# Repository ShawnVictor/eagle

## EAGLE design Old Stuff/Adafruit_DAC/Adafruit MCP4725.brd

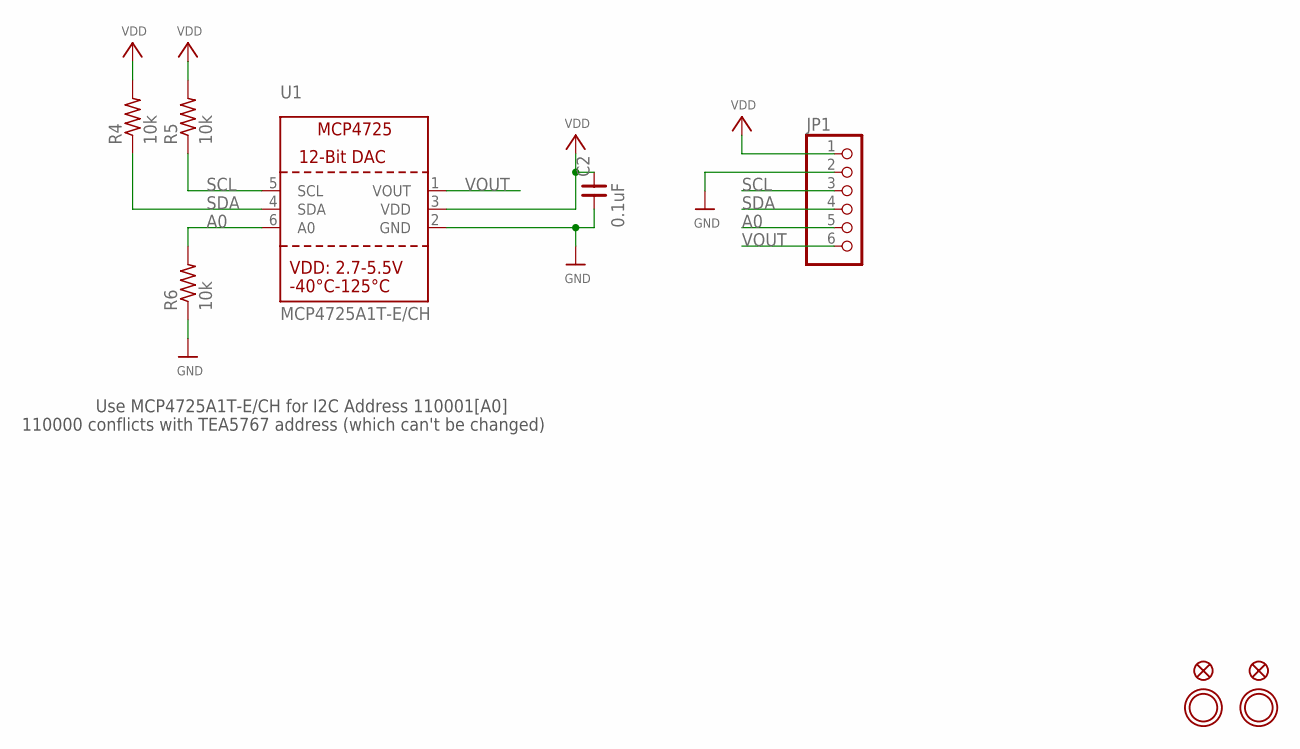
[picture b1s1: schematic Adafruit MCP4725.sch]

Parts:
C2: 0.1uF; 0805
FID1, FID2: FIDUCIAL""; FIDUCIAL_1MM
JP1: HEADER-1X670MIL; 1X06_ROUND_70
R4, R5, R6: 10k; R0805
U1: MCP4725A1T-E/CH; SOT23-6
U$7, U$8: MOUNTINGHOLE2.5; MOUNTINGHOLE_2.5_PLATED

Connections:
A0: JP1.5, R6.2, U1.6 (A0)
GND: C2.1, JP1.2, R6.1, U1.2 (GND)
SCL: JP1.3, R5.1, U1.5 (SCL)
SDA: JP1.4, R4.1, U1.4 (SDA)
VDD: C2.2, JP1.1, R4.2, R5.2, U1.3 (VDD)
VOUT: JP1.6, U1.1 (VOUT)

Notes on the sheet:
Use MCP4725A1T-E/CH for I2C Address 110001[A0]
110000 conflicts with TEA5767 address (which can't be changed)

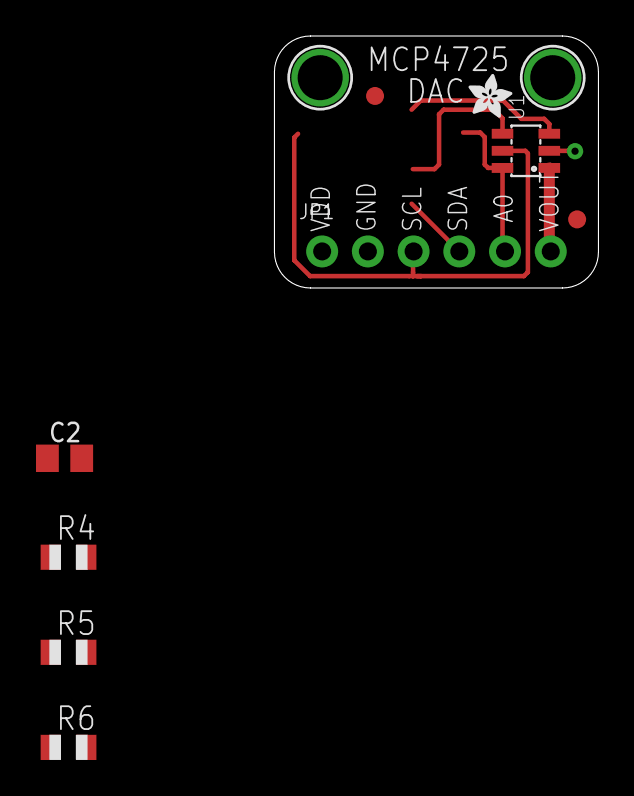
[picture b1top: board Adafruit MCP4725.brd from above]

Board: 2 copper layers, 18.0 x 14.0 mm, 11 parts (0 on the bottom side), 6 nets.

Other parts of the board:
U$11: ADAFRUIT_2.5MM

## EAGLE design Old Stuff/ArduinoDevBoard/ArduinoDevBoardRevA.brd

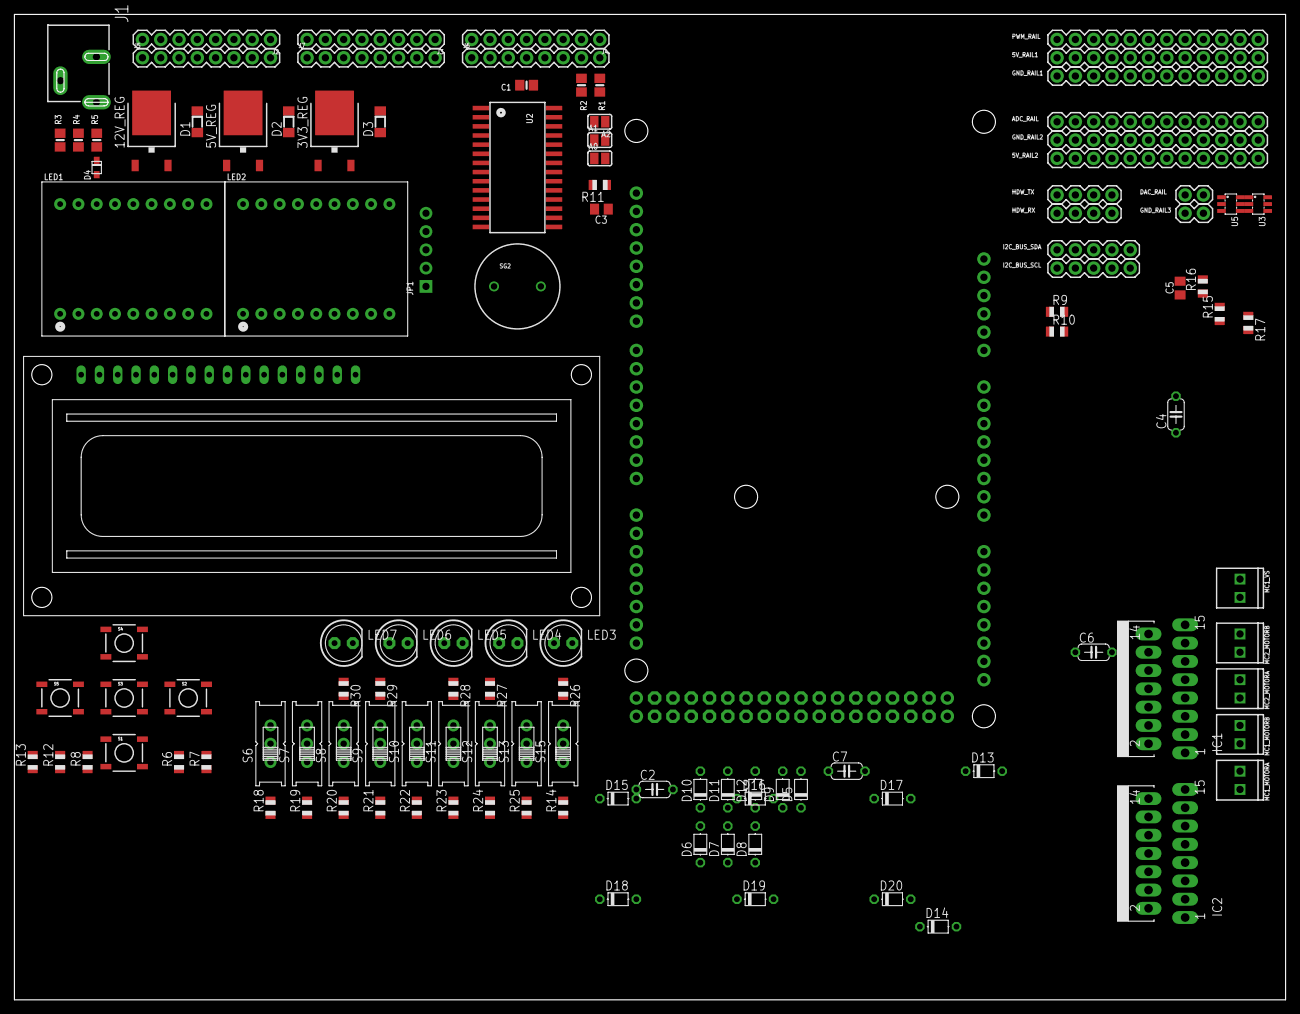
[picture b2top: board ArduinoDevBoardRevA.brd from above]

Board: 2 copper layers, 176.5 x 136.8 mm, 117 parts (1 on the bottom side), 103 nets, no tracks yet.

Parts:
3V3_REG, 5V_REG, 12V_REG: 7812DT; TO252
5V_RAIL1, 5V_RAIL2: 1X12
A0, A1, A2: SOLDERJUMPER_REFLOW_NOPASTE
ADC_RAIL: 1X12
B1: ARDUINO_MEGA_R3FULL; ARDUINO_MEGA
C1: 10uF; 0805-NO
C2, C4, C6, C7: 100nF; C050-024X044
C3, C5: 0.1uF; 0805
D1, D2, D3: SOD-123
D4: 1N4148; SOD-323F
D5, D6, D7, D8, D9, D10, D11, D12, D13, D14, D15, D16, D17, D18, D19, D20: D-5
DAC_RAIL: 1X02
GND_RAIL1, GND_RAIL2: 1X12
GND_RAIL3: 1X02
HDW_RX: 1X04
HDW_TX: 1X04
I2C_BUS_SCL, I2C_BUS_SDA: 1X05
IC1, IC2: L298; MULTIWATT-15
J1: POWER_JACKSLT; POWER_JACK_SLOT
J2, J3, J4, J5, J6, J7: 1X08
JP1: 1X05_ROUND_70
LED1, LED2: SEGMENT_STARTBUST_DUAL_KWA-541CBB
LED3, LED4, LED5, LED6, LED7: LED5MM
MC1_MOTORA, MC1_MOTORB, MC1_VS, MC2_MOTORA, MC2_MOTORB: 1X02_2.54_SCREWTERM
PWM_RAIL: 1X12
R1, R2: 10K; 0805-NO
R3, R4, R5: 47K; 0805-NO
R6, R7, R8, R12, R13: R0805
R9, R10, R11, R15, R16, R17: 10k; R0805
R14, R18, R19, R20, R21, R22, R23, R24, R25: 10K; R0805
R26, R27, R28, R29, R30: 470; R0805
S1, S2, S3, S4, S5: TACTILE_SWITCH_SMD
S6, S7, S8, S9, S10, S11, S12, S13, S15: EG1218
SG2: BUZZERPTH; BUZZER-12MM
U2: SOP28_300MIL
U3, U5: MCP4725A1T-E/CH; SOT23-6
X1: HD44780LCD-1602; LCD1602

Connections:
5V: 5V_RAIL1.1, 5V_RAIL1.2, 5V_RAIL1.3, 5V_RAIL1.4, 5V_RAIL1.5, 5V_RAIL1.6, 5V_RAIL1.7, 5V_RAIL1.8, 5V_RAIL1.9, 5V_RAIL1.10, 5V_RAIL1.11, 5V_RAIL1.12, 5V_RAIL2.1, 5V_RAIL2.2, 5V_RAIL2.3, 5V_RAIL2.4, 5V_RAIL2.5, 5V_RAIL2.6, 5V_RAIL2.7, 5V_RAIL2.8, 5V_RAIL2.9, 5V_RAIL2.10, 5V_RAIL2.11, 5V_RAIL2.12, C2.1, C3.2, C5.2, C6.1, D2.2, IC1.9, IC2.9, J3.1, J3.2, J3.3, J3.4, J3.5, J3.6, J3.7, J3.8, R9.2, R10.2, R15.2, R16.2, R17.2, S1.1, S2.1, S3.1, S4.1, S5.1, S6.S, S7.S, S8.S, S9.S, S10.S, S11.S, S12.S, S13.S, S15.S, U3.3, U5.3, U5.6
A0: A0.2, LED1.9, LED2.9, R11.2, U2.P$23, U3.6
A1: A1.2, LED1.10, LED2.10, U2.P$24
A2: A2.2, LED1.12, LED2.12, U2.P$25
ADC1: ADC_RAIL.1, B1.A0
ADC2: ADC_RAIL.2, B1.A1
ADC3: ADC_RAIL.3, B1.A2
ADC4: ADC_RAIL.4, B1.A3
ADC5: ADC_RAIL.5, B1.A4
ADC6: ADC_RAIL.6, B1.A5
ADC7: ADC_RAIL.7, B1.A6
ADC8: ADC_RAIL.8, B1.A7
ADC9: ADC_RAIL.9, B1.A8
ADC10: ADC_RAIL.10, B1.A9
ADC11: ADC_RAIL.11, B1.A10
ADC12: ADC_RAIL.12, B1.A11
BUTTON1: R6.2, S1.3
BUTTON2: R13.2, S5.3
BUTTON3: R7.2, S2.3
BUTTON4: R12.2, S4.3
BUTTON5: R8.2, S3.3
BUZZER: B1.44, SG2.-
COM0: D4.A, LED1.16, U2.P$2
COM1: LED1.11, U2.P$3
COM2: LED2.16, U2.P$4
COM3: LED2.11, U2.P$5
GND: 3V3_REG.3, 5V_REG.3, 12V_REG.3, B1.GND@0, C1.2, C2.2, C3.1, C4.2, C5.1, C6.2, C7.2, D9.A, D10.A, D11.A, D12.A, D17.A, D18.A, D19.A, D20.A, GND_RAIL1.1, GND_RAIL1.2, GND_RAIL1.3, GND_RAIL1.4, GND_RAIL1.5, GND_RAIL1.6, GND_RAIL1.7, GND_RAIL1.8, GND_RAIL1.9, GND_RAIL1.10, GND_RAIL1.11, GND_RAIL1.12, GND_RAIL2.1, GND_RAIL2.2, GND_RAIL2.3, GND_RAIL2.4, GND_RAIL2.5, GND_RAIL2.6, GND_RAIL2.7, GND_RAIL2.8, GND_RAIL2.9, GND_RAIL2.10, GND_RAIL2.11, GND_RAIL2.12, GND_RAIL3.1, GND_RAIL3.2, IC1.1, IC1.8, IC1.15, IC2.1, IC2.8, IC2.15, J1.GND@1, J1.GND@2, J5.1, J5.2, J5.3, J5.4, J5.5, J5.6, J5.7, J5.8, J6.1, J6.2, J6.3, J6.4, J6.5, J6.6, J6.7, J6.8, J7.1, J7.2, J7.3, J7.4, J7.5, J7.6, J7.7, J7.8, JP1.3, LED3.K, LED4.K, LED5.K, LED6.K, LED7.K, MC1_VS.P2, R6.1, R7.1, R8.1, R11.1, R12.1, R13.1, R14.1, R17.1, R18.1, R19.1, R20.1, R21.1, R22.1, R23.1, R24.1, R25.1, SG2.+, U2.P$1, U3.2, U5.2
HDW_RX0: B1.0, HDW_RX.1
HDW_RX1: B1.19, HDW_RX.2
HDW_RX2: B1.17, HDW_RX.3
HDW_RX3: B1.15, HDW_RX.4
HDW_TX0: B1.1, HDW_TX.1
HDW_TX1: B1.18, HDW_TX.2
HDW_TX2: B1.16, HDW_TX.3
HDW_TX3: B1.14, HDW_TX.4
unnamed: LED3.A, R26.1
unnamed: LED4.A, R27.1
unnamed: LED5.A, R28.1
unnamed: LED6.A, R29.1
unnamed: 12V_REG.2, D1.1
unnamed: LED7.A, R30.1
unnamed: B1.22, R26.2
unnamed: B1.23, R27.2
unnamed: B1.24, R28.2
unnamed: 5V_REG.2, D2.1
unnamed: 3V3_REG.2, D3.1
unnamed: D1.2, J2.1, J2.2, J2.3, J2.4, J2.5, J2.6, J2.7, J2.8
unnamed: B1.25, R29.2
unnamed: D3.2, J4.1, J4.2, J4.3, J4.4, J4.5, J4.6, J4.7, J4.8
unnamed: B1.26, R30.2
unnamed: LED1.7, LED2.7, U2.P$22
unnamed: LED1.1, LED2.1, U2.P$21
unnamed: LED1.18, LED2.18, U2.P$20
unnamed: A1.1, R3.2
unnamed: A0.1, R4.2
unnamed: LED1.13, LED2.13, U2.P$19
unnamed: LED1.6, LED2.6, U2.P$18
unnamed: D4.C, R3.1, R4.1, R5.1
unnamed: A2.1, R5.2
unnamed: LED1.17, LED2.17, U2.P$17
unnamed: LED1.15, LED2.15, U2.P$16
unnamed: LED1.14, LED2.14, U2.P$15
unnamed: LED1.2, LED2.2, U2.P$14
unnamed: LED1.4, LED2.4, U2.P$13
unnamed: LED1.5, LED2.5, U2.P$12
unnamed: LED1.8, LED2.8, U2.P$11
unnamed: JP1.5, R1.1, R2.1
unnamed: D13.A, D17.C, IC1.2, MC2_MOTORA.P1
unnamed: D14.A, D18.C, IC1.3, MC2_MOTORA.P2
unnamed: D15.A, D19.C, IC1.13, MC2_MOTORB.P1
unnamed: D16.A, D20.C, IC1.14, MC2_MOTORB.P2
unnamed: D5.A, D9.C, IC2.2, MC1_MOTORA.P1
unnamed: D6.A, D10.C, IC2.3, MC1_MOTORA.P2
unnamed: D7.A, D11.C, IC2.13, MC1_MOTORB.P1
unnamed: D8.A, D12.C, IC2.14, MC1_MOTORB.P2
unnamed: R14.2, S15.O
unnamed: C4.1, C7.1, D5.C, D6.C, D7.C, D8.C, D13.C, D14.C, D15.C, D16.C, IC1.4, IC2.4, MC1_VS.P1
unnamed: R18.2, S6.O
unnamed: R19.2, S7.O
unnamed: R20.2, S8.O
unnamed: R21.2, S9.O
unnamed: R22.2, S10.O
unnamed: R23.2, S11.O
unnamed: R24.2, S12.O
unnamed: R25.2, S13.O
PWM1: B1.2, PWM_RAIL.1
PWM2: B1.3, PWM_RAIL.2
PWM3: B1.4, PWM_RAIL.3
PWM4: B1.5, PWM_RAIL.4
PWM5: B1.6, PWM_RAIL.5
PWM6: B1.7, PWM_RAIL.6
PWM7: B1.8, PWM_RAIL.7
PWM8: B1.9, PWM_RAIL.8
PWM9: B1.10, PWM_RAIL.9
PWM10: B1.11, PWM_RAIL.10
PWM11: B1.12, PWM_RAIL.11
PWM12: B1.13, PWM_RAIL.12
SCL: B1.21, I2C_BUS_SCL.1, I2C_BUS_SCL.2, I2C_BUS_SCL.3, I2C_BUS_SCL.4, I2C_BUS_SCL.5, JP1.1, R1.2, R10.1, R16.1, U2.P$26, U3.5, U5.5
SDA: B1.20, I2C_BUS_SDA.1, I2C_BUS_SDA.2, I2C_BUS_SDA.3, I2C_BUS_SDA.4, I2C_BUS_SDA.5, JP1.2, R2.2, R9.1, R15.1, U2.P$27, U3.4, U5.4
VDD: C1.1, JP1.4, U2.P$28
VIN: 3V3_REG.1, 5V_REG.1, 12V_REG.1, J1.PWR
VOUT1: DAC_RAIL.1, U3.1
VOUT2: DAC_RAIL.2, U5.1

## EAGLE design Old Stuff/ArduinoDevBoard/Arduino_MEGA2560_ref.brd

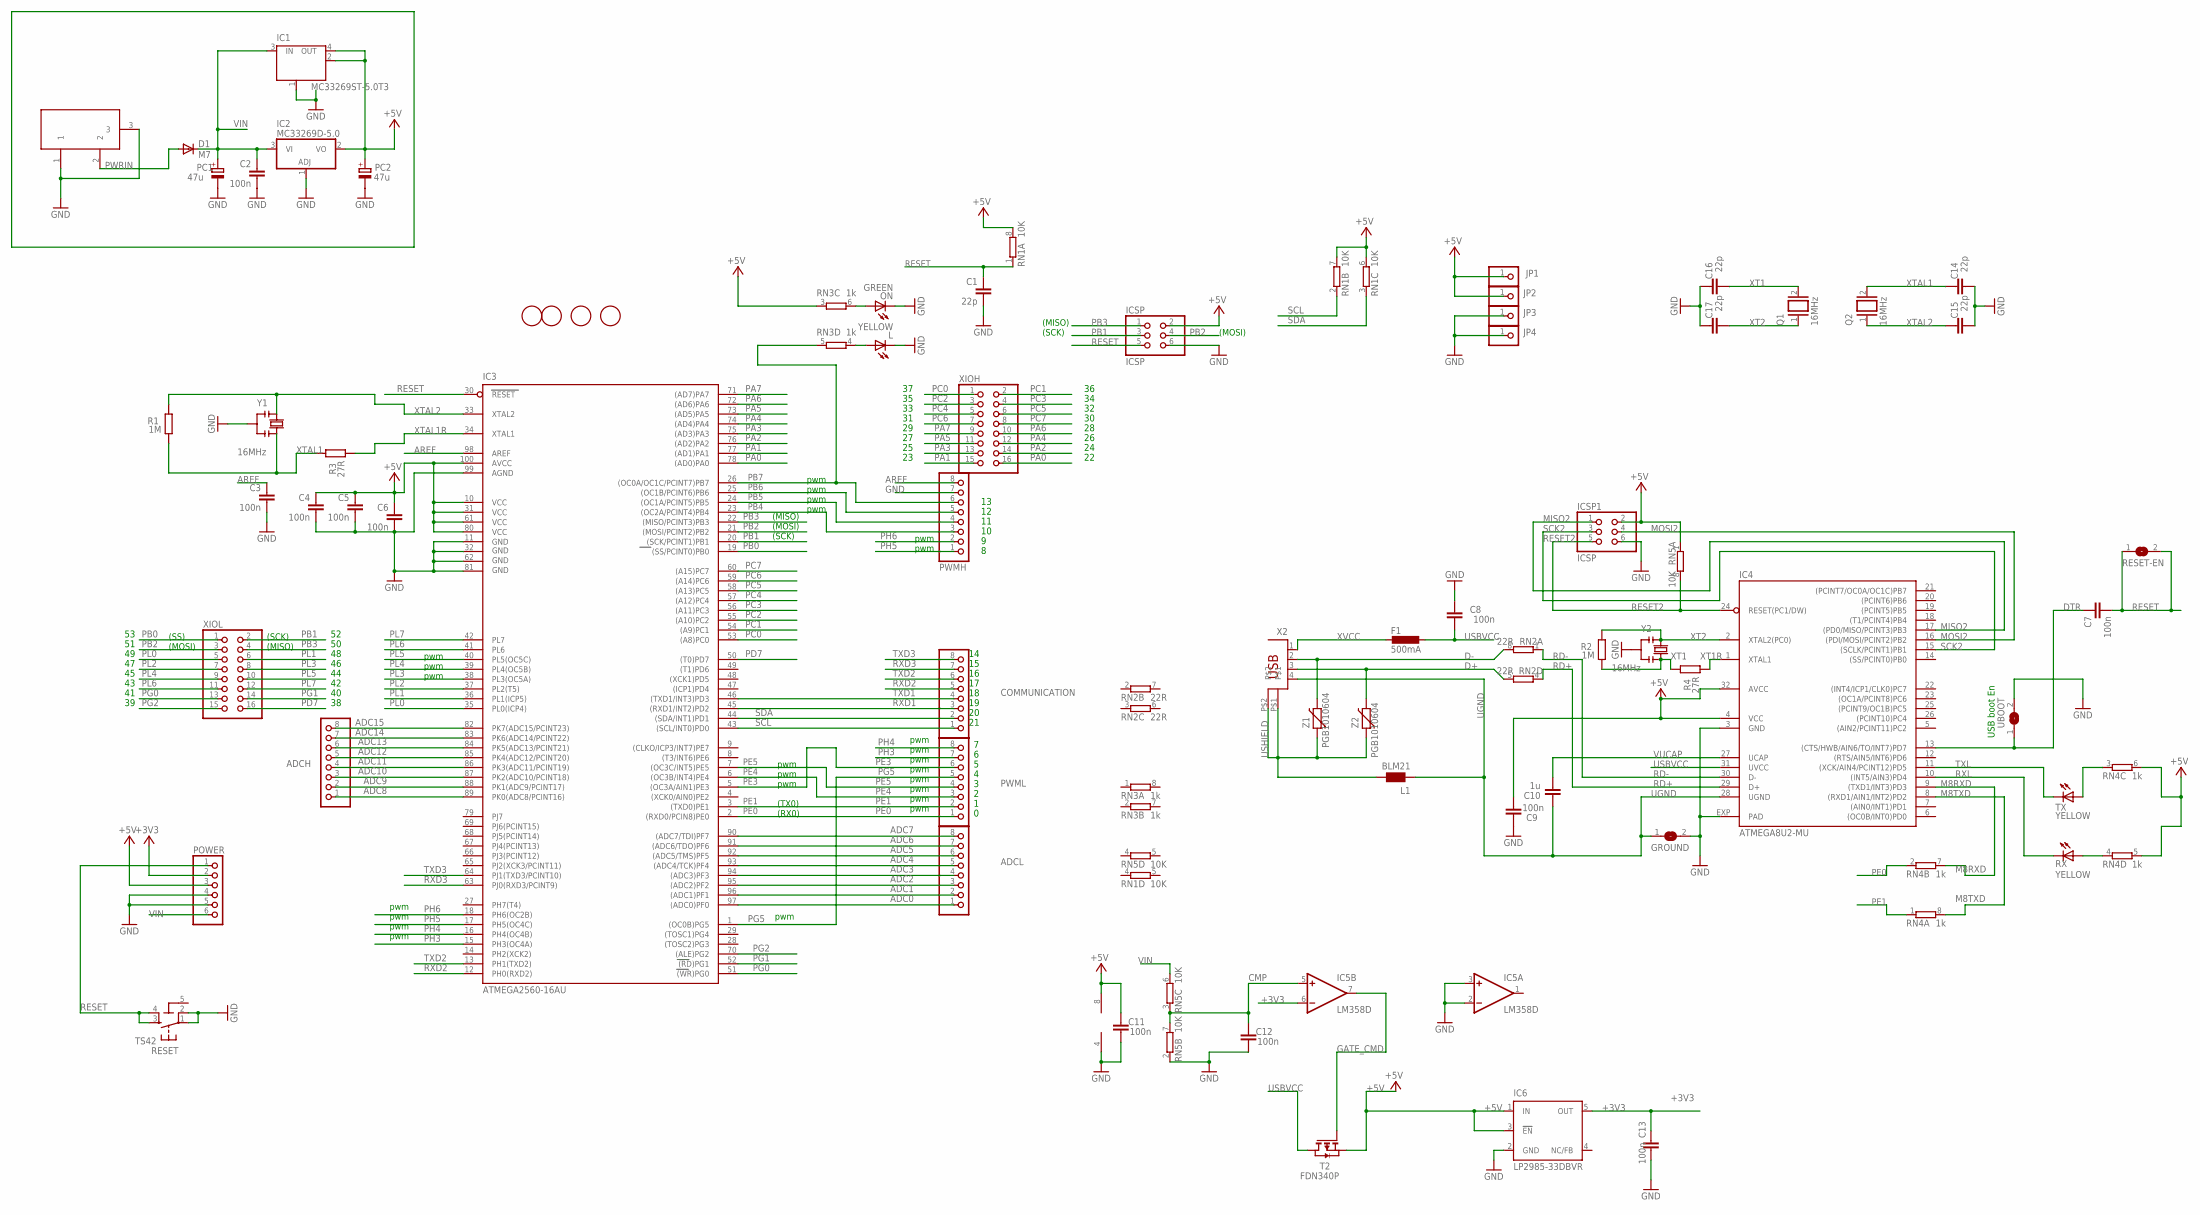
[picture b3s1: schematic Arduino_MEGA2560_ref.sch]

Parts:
ADCH: PINHD-1X8; 1X08
ADCL: PINHD-1X8; 1X08
C1, C14, C15, C16, C17: 22p; C0603-ROUND
C2, C3, C4, C5, C6, C7, C9, C12, C13: 100n; C0603-ROUND
C8, C11: 100n; C0603
C10: 1u; C0603-ROUND
COMMUNICATION: PINHD-1X8; 1X08
D1: M7; SMB
F1: 500mA; L1812
GROUND: SJ
IC1: MC33269ST-5.0T3; SOT223
IC2: MC33269D-5.0; DPACK
IC3: ATMEGA2560-16AU; TQFP100
IC4: ATMEGA8U2-MU; QFN32
IC5: LM358D; SO08
IC6: LP2985-33DBVR; SOT23-DBV
ICSP, ICSP1: ICSP; 2X03
JP1, JP2, JP3, JP4: PINHD-1X1; 1X01
L: YELLOW; CHIP-LED0805
L1: BLM21; 0805
ON: GREEN; CHIP-LED0805
PC1, PC2: 47u; PANASONIC_D
POWER: PINHD-1X6; 1X06
PWMH: PINHD-1X8; 1X08
PWML: PINHD-1X8; 1X08
Q1, Q2: 16MHz; QS
R1, R2: 1M; R0603-ROUND
R3, R4: 27R; R0603-ROUND
RESET: TS42
RESET-EN: SJ
RN1, RN5: 10K; CAT16
RN2: 22R; CAY16
RN3, RN4: 1k; CAY16
RX: YELLOW; CHIP-LED0805
T2: FDN340P; SOT-23
TX: YELLOW; CHIP-LED0805
U$2, U$3, U$4, U$5: FIDUCIALMOUNT; FIDUCIA-MOUNT
UBOOT: SJ
X1: DC21MMX; DC-21MM
X2: PN61729
XIOH: PINHD-2X8; 2X08
XIOL: PINHD-2X8; 2X08
Y1, Y2: 16MHz; RESONATOR
Z1, Z2: PGB1010604; CT/CN0603

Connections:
5-GND: RESET.5 (5-GND)
+3V3: C13.2, IC5.6 (-IN), IC6.5 (OUT), POWER.2
+5V: C4.1, C5.1, C6.1, C9.1, C11.2, IC1.2 (OUT), IC1.4 (OUT), IC2.2 (VO), IC3.10 (VCC), IC3.31 (VCC1), IC3.61 (VCC2), IC3.80 (VCC3), IC3.100 (AVCC), IC4.4 (VCC), IC4.32 (AVCC), IC5.8 (V+), IC6.1 (IN), IC6.3 (!EN), ICSP.2, ICSP1.2, JP1.1, JP2.1, PC2.+, POWER.3, RN1.6 (2), RN1.7 (2), RN1.8 (2), RN3.3 (1), RN4.5 (2), RN4.6 (2), RN5.1, T2.2 (S)
ADC0: ADCL.1, IC3.97 ((ADC0)PF0)
ADC1: ADCL.2, IC3.96 ((ADC1)PF1)
ADC2: ADCL.3, IC3.95 ((ADC2)PF2)
ADC3: ADCL.4, IC3.94 ((ADC3)PF3)
ADC4: ADCL.5, IC3.93 ((ADC4/TCK)PF4)
ADC5: ADCL.6, IC3.92 ((ADC5/TMS)PF5)
ADC6: ADCL.7, IC3.91 ((ADC6/TDO)PF6)
ADC7: ADCL.8, IC3.90 ((ADC7/TDI)PF7)
ADC8: ADCH.1, IC3.89 (PK0(ADC8/PCINT16))
ADC9: ADCH.2, IC3.88 (PK1(ADC9/PCINT17))
ADC10: ADCH.3, IC3.87 (PK2(ADC10/PCINT18))
ADC11: ADCH.4, IC3.86 (PK3(ADC11/PCINT19))
ADC12: ADCH.5, IC3.85 (PK4(ADC12/PCINT20))
ADC13: ADCH.6, IC3.84 (PK5(ADC13/PCINT21))
ADC14: ADCH.7, IC3.83 (PK6(ADC14/PCINT22))
ADC15: ADCH.8, IC3.82 (PK7(ADC15/PCINT23))
AREF: C3.1, IC3.98 (AREF), PWMH.8
CMP: C12.2, IC5.5 (+IN), RN5.3 (1), RN5.7 (2)
D+: RN2.5 (2), X2.3, Z2.2
D-: RN2.8 (2), X2.2, Z1.2
DTR: C7.1, IC4.13 ((CTS/HWB/AIN6/TO/INT7)PD7), UBOOT.1
GATE_CMD: IC5.7 (OUT), T2.3 (G)
GND: C1.2, C2.2, C3.2, C4.2, C5.2, C6.2, C8.2, C9.2, C11.1, C12.1, C13.1, C14.1, C15.1, C16.2, C17.2, GROUND.2, IC1.1 (GND/ADJ), IC2.1 (ADJ), IC3.11 (GND), IC3.32 (GND1), IC3.62 (GND2), IC3.81 (GND3), IC3.99 (AGND), IC4.3 (GND), IC4.EXP (PAD), IC5.2 (-IN), IC5.3 (+IN), IC5.4 (V-), IC6.2 (GND), ICSP.6, ICSP1.6, JP3.1, JP4.1, L.C, ON.C, PC1.-, PC2.-, POWER.4, POWER.5, PWMH.7, RESET.1, RESET.2, RN5.2 (1), UBOOT.2, X1.1, X1.3, Y1.2, Y2.2
M8RXD: IC4.9 ((TXD1/INT3)PD3), RN4.7 (2)
M8TXD: IC4.8 ((RXD1/AIN1/INT2)PD2), RN4.8 (2)
MISO2: IC4.17 ((PD0/MISO/PCINT3)PB3), ICSP1.1
MOSI2: IC4.16 ((PDI/MOSI/PCINT2)PB2), ICSP1.4
unnamed: L.A, RN3.4 (1)
unnamed: ON.A, RN3.6 (2)
unnamed: RN4.4 (1), RX.A
unnamed: RN4.3 (1), TX.A
PA0: IC3.78 ((AD0)PA0), XIOH.16
PA1: IC3.77 ((AD1)PA1), XIOH.15
PA2: IC3.76 ((AD2)PA2), XIOH.14
PA3: IC3.75 ((AD3)PA3), XIOH.13
PA4: IC3.74 ((AD4)PA4), XIOH.12
PA5: IC3.73 ((AD5)PA5), XIOH.11
PA6: IC3.72 ((AD6)PA6), XIOH.10
PA7: IC3.71 ((AD7)PA7), XIOH.9
PB0: IC3.19 ((SS/PCINT0)PB0), XIOL.1
PB1: IC3.20 ((SCK/PCINT1)PB1), ICSP.3, XIOL.2
PB2: IC3.21 ((MOSI/PCINT2)PB2), ICSP.4, XIOL.3
PB3: IC3.22 ((MISO/PCINT3)PB3), ICSP.1, XIOL.4
PB4: IC3.23 ((OC2A/PCINT4)PB4), PWMH.3
PB5: IC3.24 ((OC1A/PCINT5)PB5), PWMH.4
PB6: IC3.25 ((OC1B/PCINT6)PB6), PWMH.5
PB7: IC3.26 ((OC0A/OC1C/PCINT7)PB7), PWMH.6, RN3.5 (2)
PC0: IC3.53 ((A8)PC0), XIOH.1
PC1: IC3.54 ((A9)PC1), XIOH.2
PC2: IC3.55 ((A10)PC2), XIOH.3
PC3: IC3.56 ((A11)PC3), XIOH.4
PC4: IC3.57 ((A12)PC4), XIOH.5
PC5: IC3.58 ((A13)PC5), XIOH.6
PC6: IC3.59 ((A14)PC6), XIOH.7
PC7: IC3.60 ((A15)PC7), XIOH.8
PD7: IC3.50 ((T0)PD7), XIOL.16
PE0: IC3.2 ((RXD0/PCIN8)PE0), PWML.1, RN4.2 (1)
PE1: IC3.3 ((TXD0)PE1), PWML.2, RN4.1
PE3: IC3.5 ((OC3A/AIN1)PE3), PWML.6
PE4: IC3.6 ((OC3B/INT4)PE4), PWML.3
PE5: IC3.7 ((OC3C/INT5)PE5), PWML.4
PG0: IC3.51 ((WR)PG0), XIOL.13
PG1: IC3.52 ((RD)PG1), XIOL.14
PG2: IC3.70 ((ALE)PG2), XIOL.15
PG5: IC3.1 ((OC0B)PG5), PWML.5
PH3: IC3.15 (PH3(OC4A)), PWML.7
PH4: IC3.16 (PH4(OC4B)), PWML.8
PH5: IC3.17 (PH5(OC4C)), PWMH.1
PH6: IC3.18 (PH6(OC2B)), PWMH.2
PL0: IC3.35 (PL0(ICP4)), XIOL.5
PL1: IC3.36 (PL1(ICP5)), XIOL.6
PL2: IC3.37 (PL2(T5)), XIOL.7
PL3: IC3.38 (PL3(OC5A)), XIOL.8
PL4: IC3.39 (PL4(OC5B)), XIOL.9
PL5: IC3.40 (PL5(OC5C)), XIOL.10
PL6: IC3.41 (PL6), XIOL.11
PL7: IC3.42 (PL7), XIOL.12
PWRIN: D1.A, X1.2
RD+: IC4.29 (D+), RN2.4 (1)
RD-: IC4.30 (D-), RN2.1
RESET: C1.1, C7.2, IC3.30 (RESET), ICSP.5, POWER.1, RESET.3, RESET.4, RESET-EN.1, RESET-EN.2, RN1.1
RESET2: IC4.24 (RESET(PC1/DW)), ICSP1.5, RN5.8 (2)
RXD1: COMMUNICATION.3, IC3.45 ((RXD1/INT2)PD2)
RXD2: COMMUNICATION.5, IC3.12 (PH0(RXD2))
RXD3: COMMUNICATION.7, IC3.63 (PJ0(RXD3/PCINT9))
RXL: IC4.10 ((INT5/AIN3)PD4), RX.C
SCK2: IC4.15 ((SCLK/PCINT1)PB1), ICSP1.3
SCL: COMMUNICATION.1, IC3.43 ((SCL/INT0)PD0), RN1.2 (1)
SDA: COMMUNICATION.2, IC3.44 ((SDA/INT1)PD1), RN1.3 (1)
TXD1: COMMUNICATION.4, IC3.46 ((TXD1/INT3)PD3)
TXD2: COMMUNICATION.6, IC3.13 (PH1(TXD2))
TXD3: COMMUNICATION.8, IC3.64 (PJ1(TXD3/PCINT10))
TXL: IC4.11 ((XCK/AIN4/PCINT12)PD5), TX.C
UGND: C10.2, GROUND.1, IC4.28 (UGND), L1.1, X2.4
USBVCC: C8.1, F1.1, IC4.31 (UVCC), T2.1 (D)
USHIELD: L1.2, X2.P$1, X2.P$2, Z1.1, Z2.1
VIN: C2.1, D1.C, IC1.3 (IN), IC2.3 (VI), PC1.+, POWER.6, RN5.6 (2)
VUCAP: C10.1, IC4.27 (UCAP)
XT1: C16.1, Q1.2, R2.1, R4.2, Y2.3
XT1R: IC4.1 (XTAL1), R4.1
XT2: C17.1, IC4.2 (XTAL2(PC0)), Q1.1, R2.2, Y2.1
XTAL1: C14.2, Q2.2, R1.1, R3.2, Y1.3
XTAL1R: IC3.34 (XTAL1), R3.1
XTAL2: C15.2, IC3.33 (XTAL2), Q2.1, R1.2, Y1.1
XVCC: F1.2, X2.1

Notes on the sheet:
(SCK)
(MISO)
(MOSI)
pwm
(TX0)
(RX0)
(SS)
USB boot En

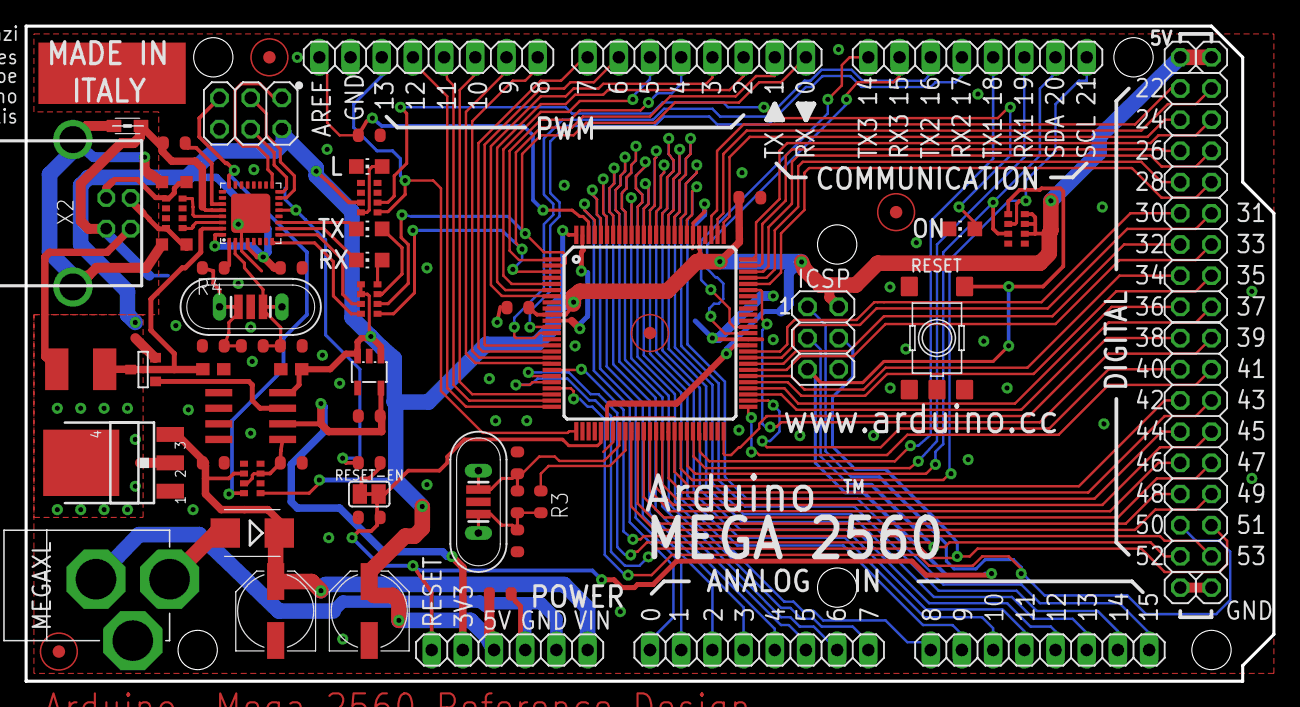
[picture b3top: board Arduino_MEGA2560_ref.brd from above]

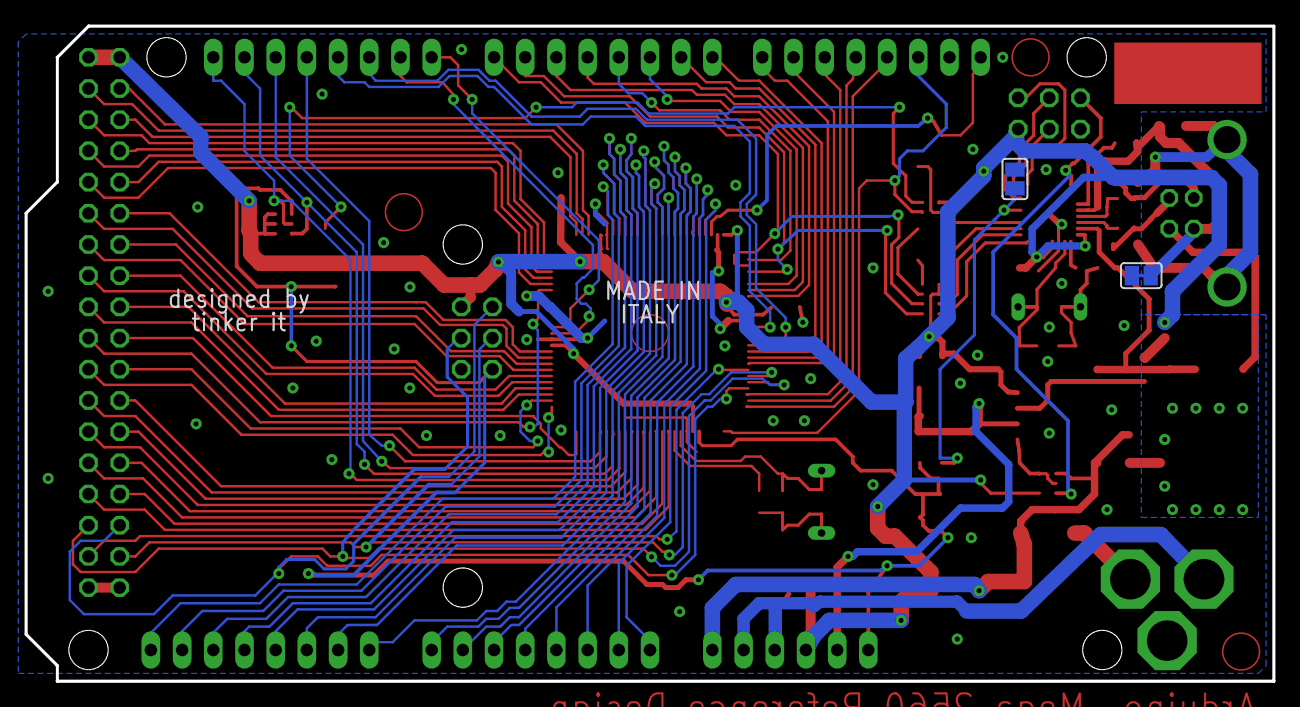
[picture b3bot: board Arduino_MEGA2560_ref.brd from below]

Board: 2 copper layers, 101.6 x 53.3 mm, 72 parts (2 on the bottom side), 107 nets.

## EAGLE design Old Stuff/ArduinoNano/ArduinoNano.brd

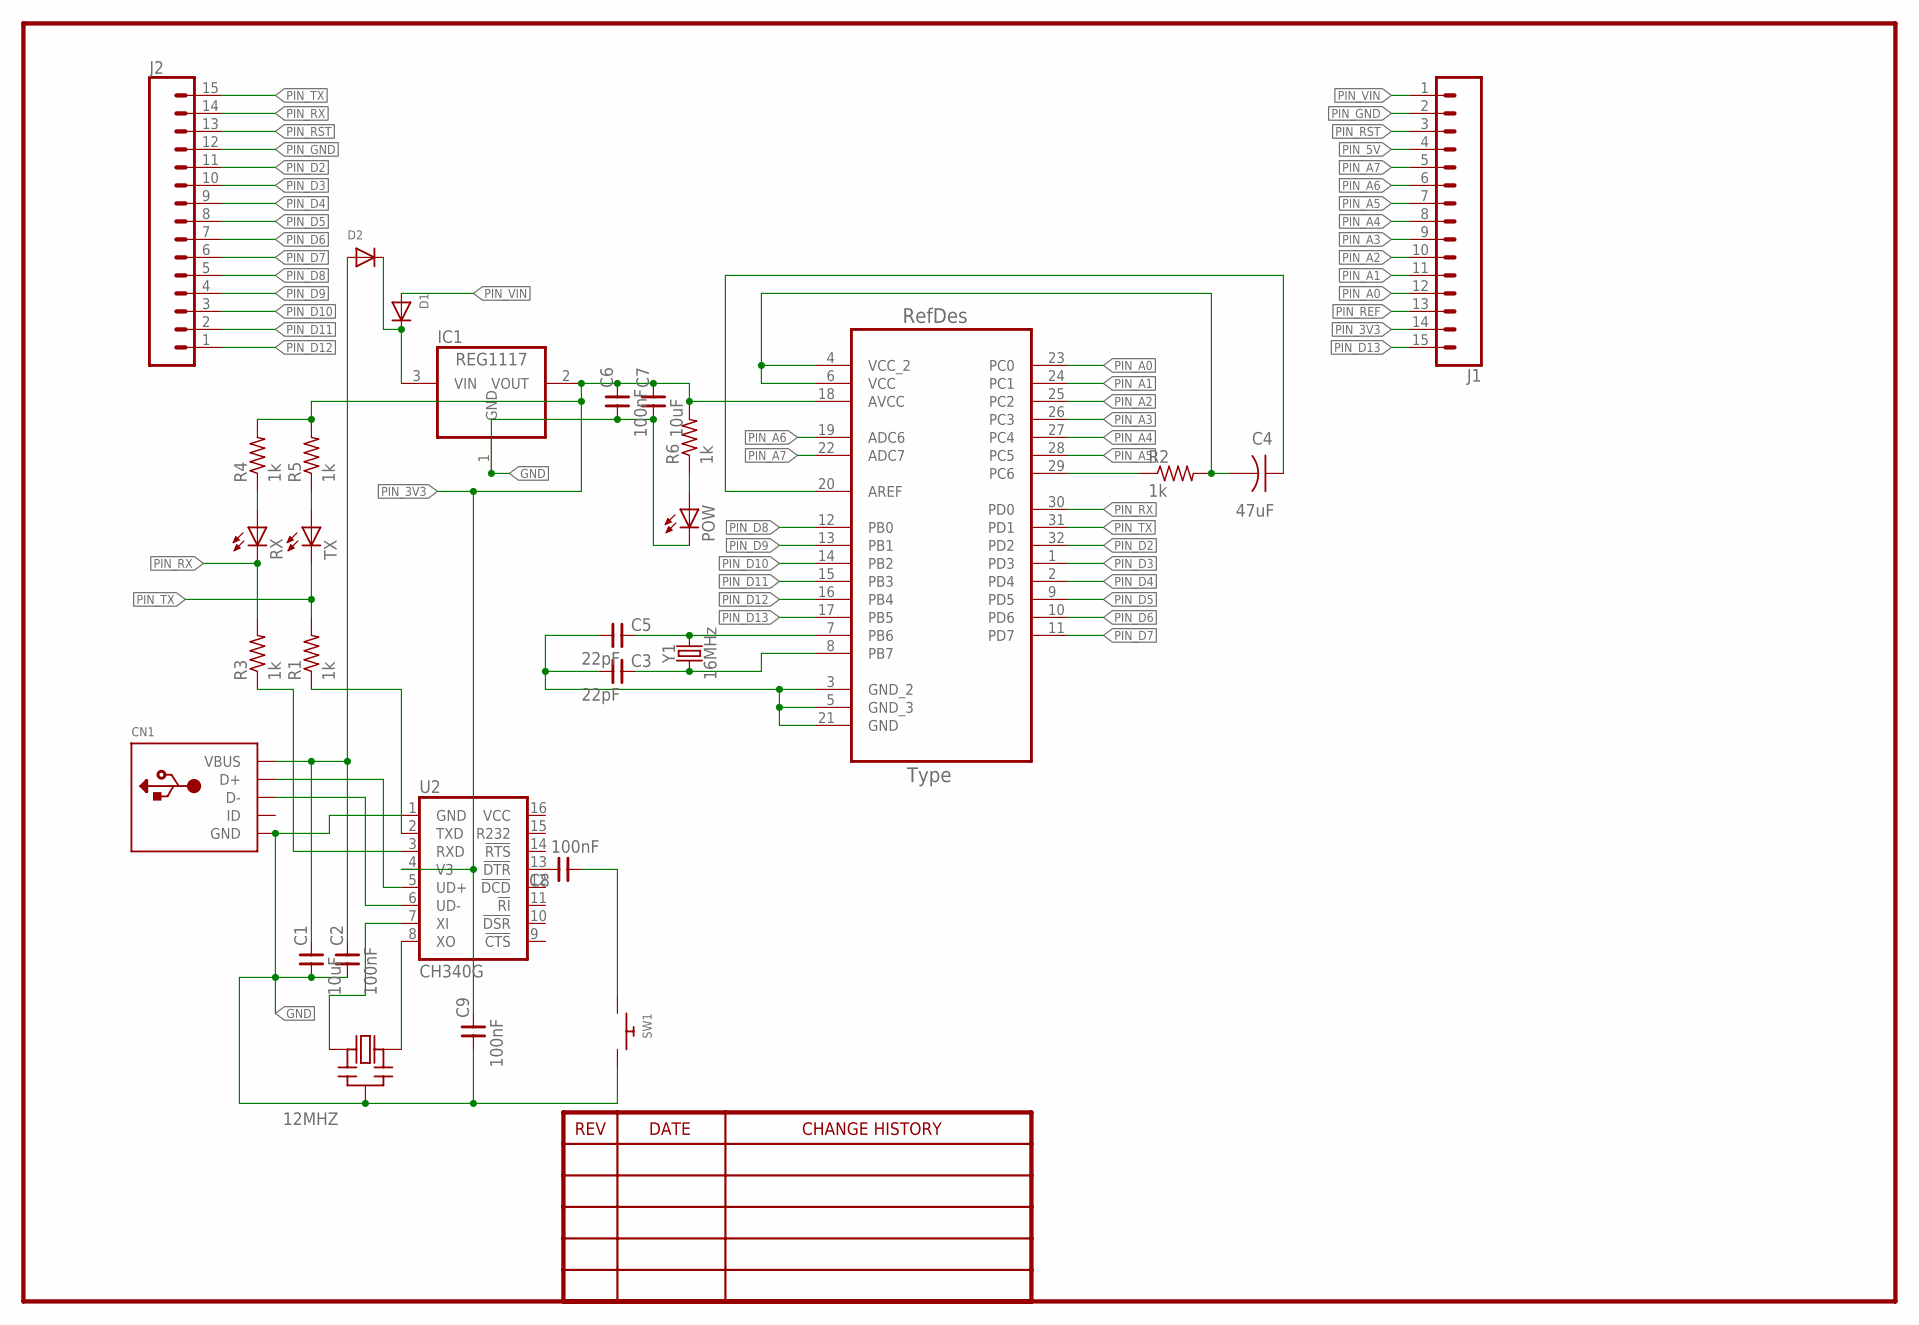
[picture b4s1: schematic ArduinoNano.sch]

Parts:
12MHZ: CERMOSCILL-THM; CERM_OSC
C1, C7: 10uF; 0603
C2, C6, C8, C9: 100nF; 0603
C3, C5: 22pF; 0603
C4: 47uF; C1210
CN1: USBMINIB; USB-MINIB
D1, D2: DIODESOD-323F; SOD-323F
IC1: REG1117; SOT223
J1, J2: CONN_15; 1X15
POW: LEDCHIP-LED0603; CHIP-LED0603
R1, R2, R3, R4, R5, R6: 1k; R0603
RX: LEDCHIPLED_0603; CHIPLED_0603
SW1: SWITCH_PUSHBUTTONEVQ-PE; TACT_PANA-EVQ
TX: LEDCHIPLED_0603; CHIPLED_0603
U1: ATMEGA328P-AU; QFP80P900X900X120-32N
U2: CH340G; SO016
Y1: 16MHz; HC49US

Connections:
GND: 12MHZ.P$2 (GND), C1.1, C2.1, C6.1, C7.1, C9.1, CN1.GND, IC1.1 (GND), POW.C, SW1.P$2, U2.1 (GND)
unnamed: C5.2, U1.7 (PB6), Y1.2
unnamed: C3.2, U1.8 (PB7), Y1.1
unnamed: C3.1, C5.1, U1.3 (GND_2), U1.5 (GND_3), U1.21 (GND)
unnamed: C4.1, U1.20 (AREF)
unnamed: R2.1, U1.29 (PC6)
unnamed: C4.2, R2.2, U1.4 (VCC_2), U1.6 (VCC)
unnamed: R4.1, RX.A
unnamed: R5.1, TX.A
unnamed: 12MHZ.P$1 (IN), U2.7 (XI)
unnamed: C1.2, C2.2, CN1.VBUS, D2.A
unnamed: CN1.D+, U2.5 (UD+)
unnamed: CN1.D-, U2.6 (UD-)
unnamed: 12MHZ.P$3 (OUT), U2.8 (XO)
unnamed: R3.1, U2.3 (RXD)
unnamed: R1.1, U2.2 (TXD)
unnamed: D1.C, D2.C, IC1.3 (VIN)
unnamed: C8.2, U2.13 (!DTR)
unnamed: POW.A, R6.1
unnamed: C8.1, SW1.P$1
PIN_3V3: C6.2, C7.2, C9.2, IC1.2 (VOUT), J1.14, R4.2, R5.2, R6.2, U1.18 (AVCC), U2.4 (V3)
PIN_5V: J1.4
PIN_A0: J1.12, U1.23 (PC0)
PIN_A1: J1.11, U1.24 (PC1)
PIN_A2: J1.10, U1.25 (PC2)
PIN_A3: J1.9, U1.26 (PC3)
PIN_A4: J1.8, U1.27 (PC4)
PIN_A5: J1.7, U1.28 (PC5)
PIN_A6: J1.6, U1.19 (ADC6)
PIN_A7: J1.5, U1.22 (ADC7)
PIN_D2: J2.11, U1.32 (PD2)
PIN_D3: J2.10, U1.1 (PD3)
PIN_D4: J2.9, U1.2 (PD4)
PIN_D5: J2.8, U1.9 (PD5)
PIN_D6: J2.7, U1.10 (PD6)
PIN_D7: J2.6, U1.11 (PD7)
PIN_D8: J2.5, U1.12 (PB0)
PIN_D9: J2.4, U1.13 (PB1)
PIN_D10: J2.3, U1.14 (PB2)
PIN_D11: J2.2, U1.15 (PB3)
PIN_D12: J2.1, U1.16 (PB4)
PIN_D13: J1.15, U1.17 (PB5)
PIN_GND: J1.2, J2.12
PIN_REF: J1.13
PIN_RST: J1.3, J2.13
PIN_RX: J2.14, R3.2, RX.C, U1.30 (PD0)
PIN_TX: J2.15, R1.2, TX.C, U1.31 (PD1)
PIN_VIN: D1.A, J1.1

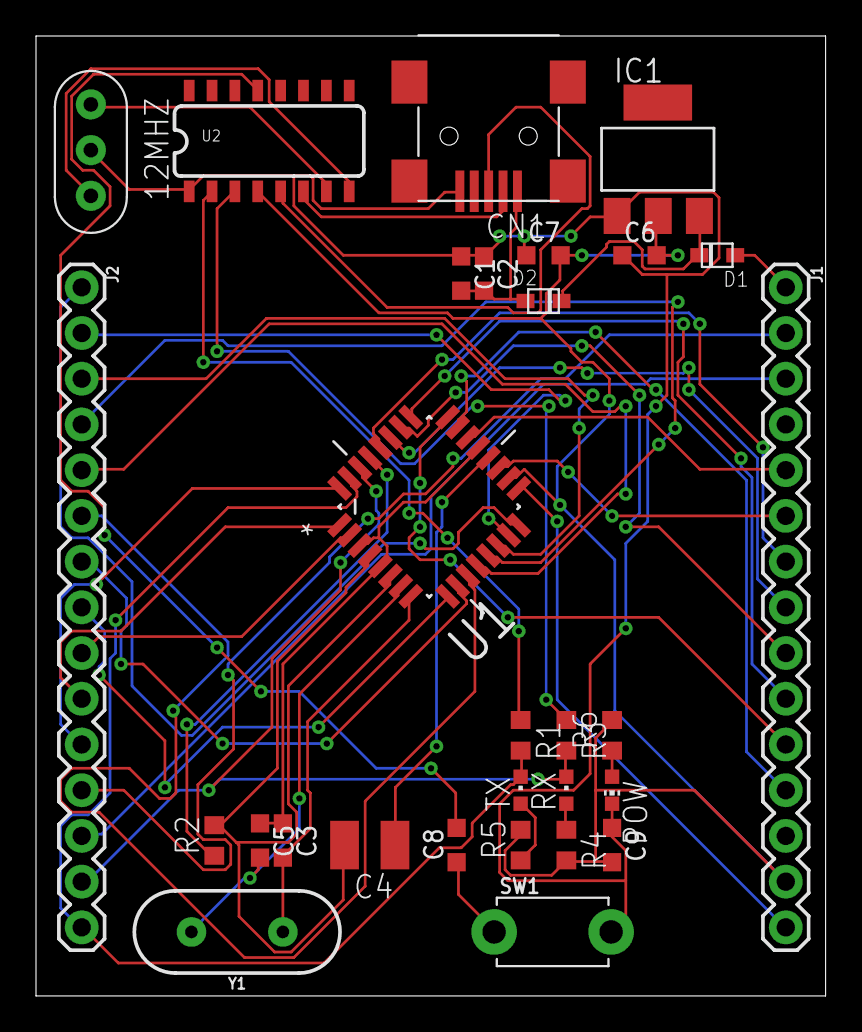
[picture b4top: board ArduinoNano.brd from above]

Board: 2 copper layers, 43.9 x 53.3 mm, 29 parts (0 on the bottom side), 46 nets.

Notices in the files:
parts and their libraries:
SparkFun-Boards: Licensing: Creative Commons ShareAlike 4.0 International - https://creativecommons.org/licenses/by-sa/4.0
MAX9812: License : GNU General Public License version 2 (see bottom)
dframes: Copyright (C) 2004, Bob Starr (bobstarr@mindspring.com)
